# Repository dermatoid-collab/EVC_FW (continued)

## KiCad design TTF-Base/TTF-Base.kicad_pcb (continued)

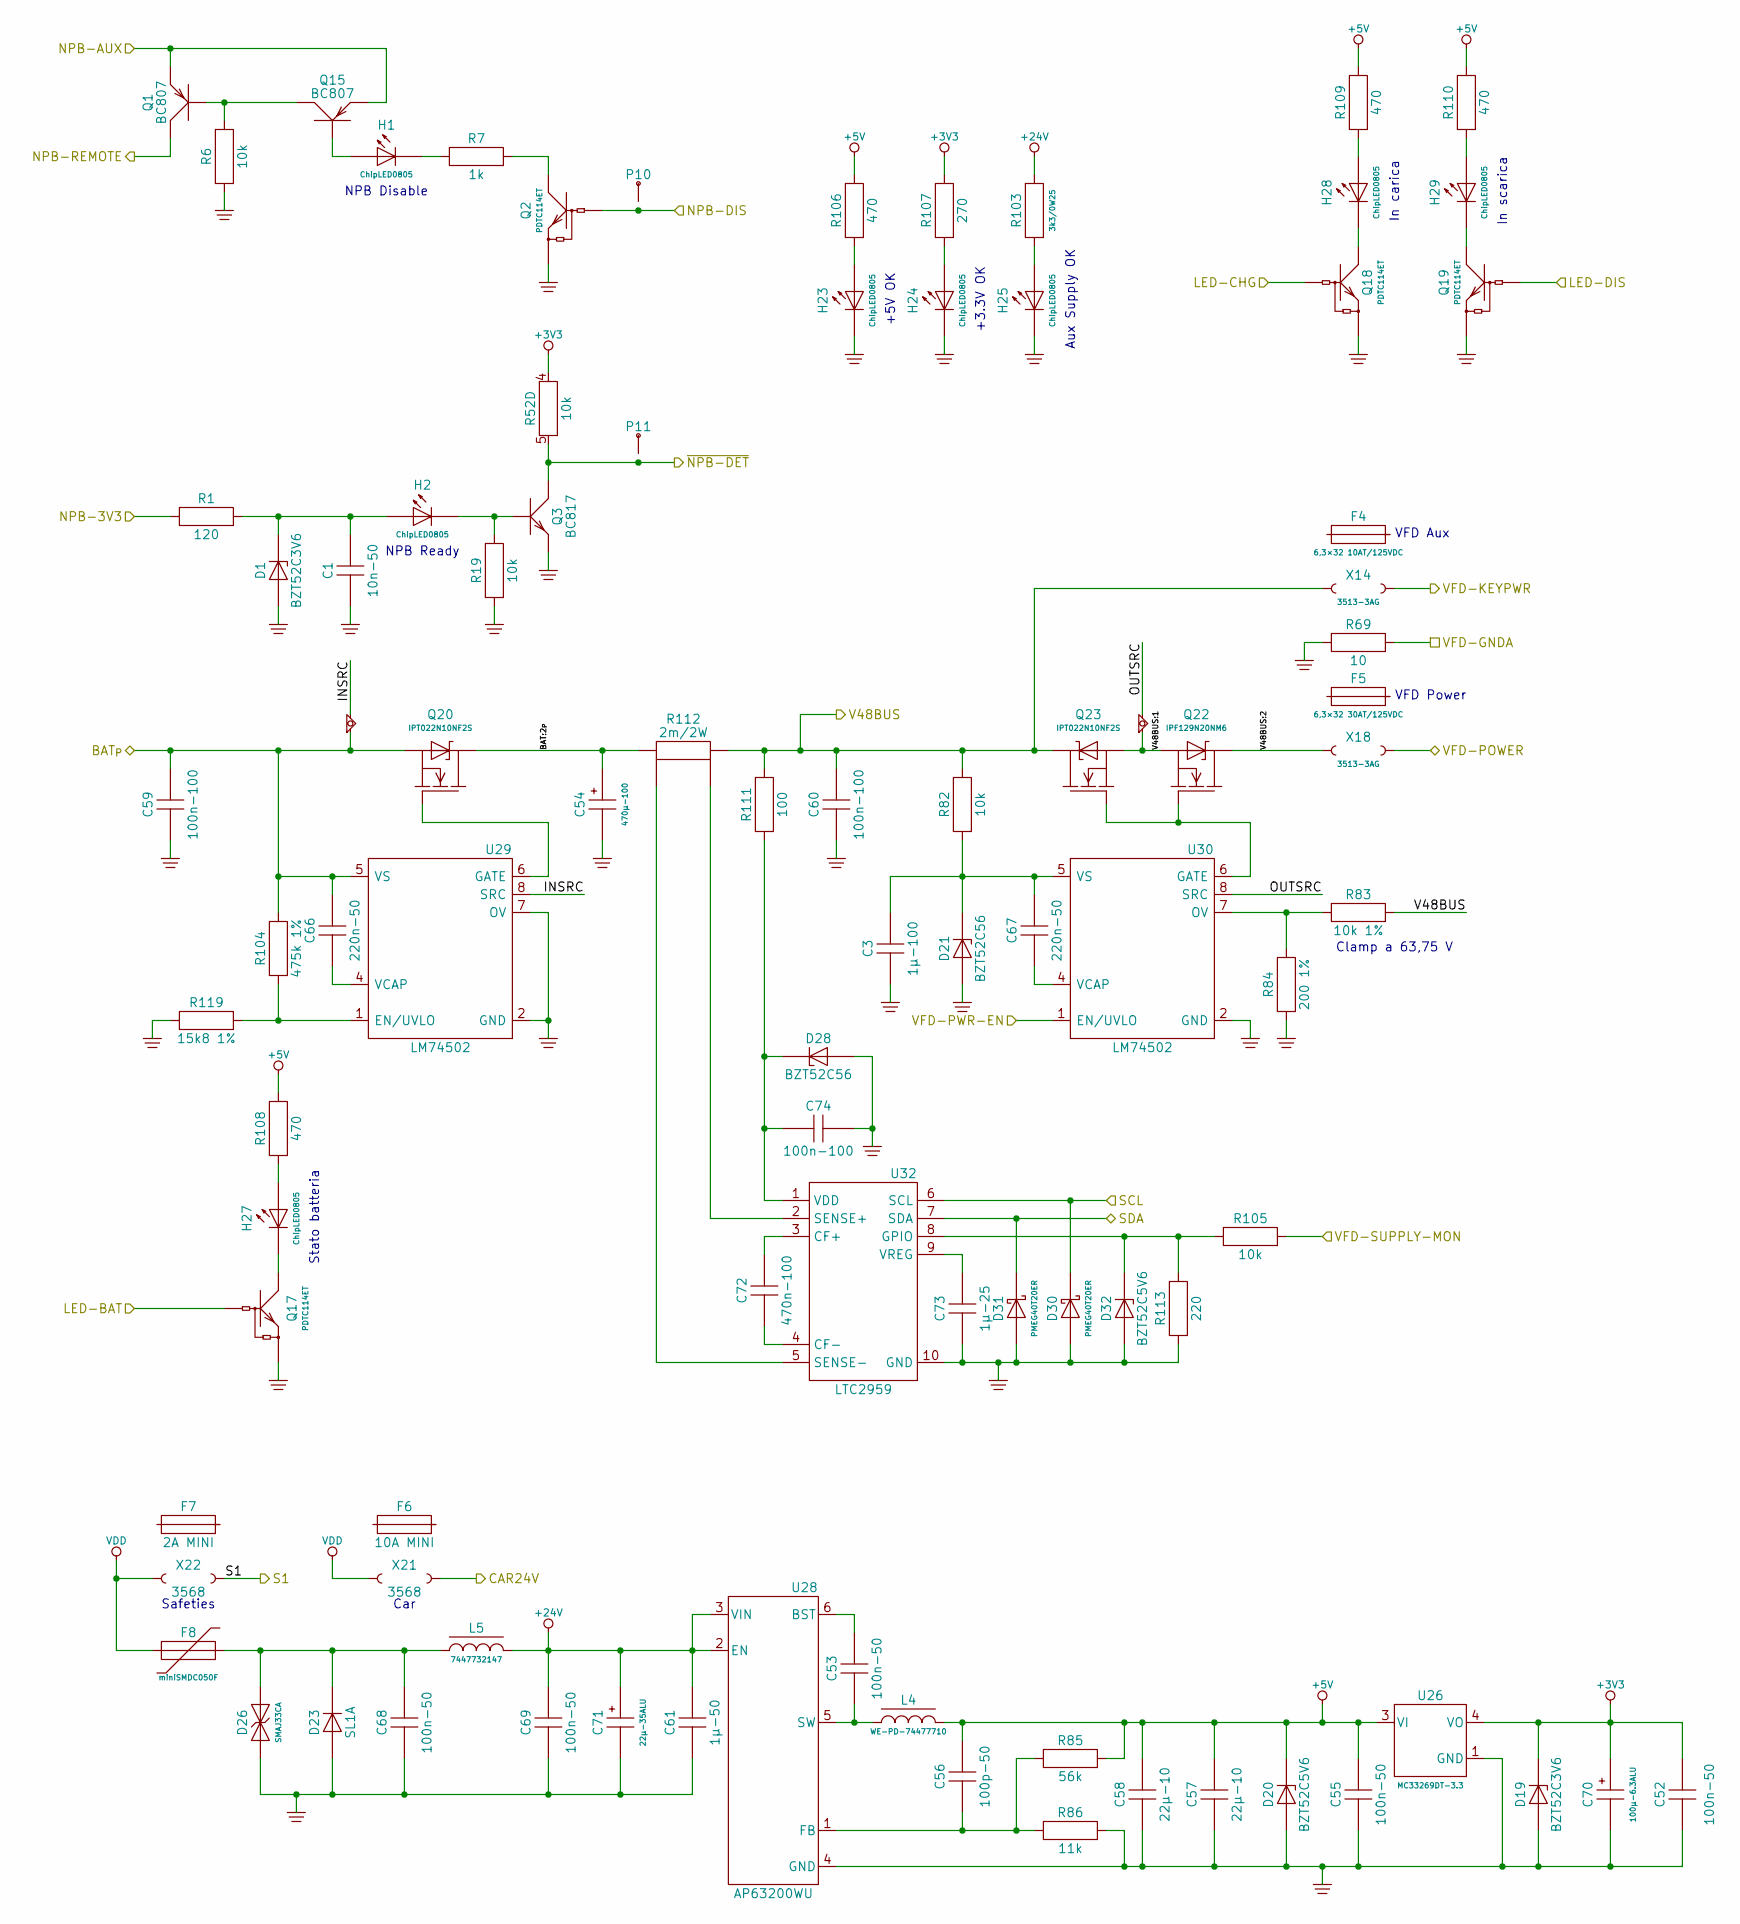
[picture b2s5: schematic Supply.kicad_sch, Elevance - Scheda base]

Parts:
C1: 10n-50; C0603
C3: 1µ-100; C1206
C52, C53, C55, C68, C69: 100n-50; C0603
C54: 470µ-100; CPAlu-12.5x25P5
C56: 100p-50; C0603
C57, C58: 22µ-10; C0805
C59, C60, C74: 100n-100; C1206
C61: 1µ-50; C1206
C66, C67: 220n-50; C0603
C70: 100µ-6.3ALU; CPV-5x5.5
C71: 22µ-35ALU; CPV-5x5.5
C72: 470n-100; C0805
C73: 1µ-25; C0603
D1, D19: BZT52C3V6; SOD123
D20, D32: BZT52C5V6; SOD123
D21, D28: BZT52C56; SOD123
D23: SL1A; SOD123FL
D26: SMAJ33CA; DO214AC-NPOL
D30, D31: PMEG40T20ER; NXP-SOD123W
EQUI1, EQUI4: EQUIPOT; Equipot-04
F4: 6,3×32 10AT/125VDC; 3AG-Fuse
F5: 6,3×32 30AT/125VDC; 3AG-Fuse
F6: 10A MINI; MINI-Fuse
F7: 2A MINI; MINI-Fuse
F8: miniSMDC050F; miniSMDC
H1, H2, H23, H24, H25, H27, H28, H29: ChipLED0805; Chipled-0805
L4: WE-PD-74477710; WE-PD-7345A
L5: 7447732147; WE-PD2-3521
P10, P11: TestPoint; PinTst
Q1, Q15: BC807; TO236-BEC
Q2, Q17, Q18, Q19: PDTC114ET; TO236-BEC
Q3: BC817; TO236-BEC
Q20, Q23: IPT022N10NF2S; Infineon-PG-HSOF-8-10
Q22: IPF129N20NM6; Infineon-TO263-7-GSSxSSSD
R1: 120; R0603
R6, R19, R82, R105: 10k; R0603
R7: 1k; R0603
R52: 10k; KMY-RAC164D
R69: 10; R0603
R83: 10k 1%; R0603
R84: 200 1%; R0603
R85: 56k; R0603
R86: 11k; R0603
R103: 3k3/0W25; R1206
R104: 475k 1%; R0603
R106, R108, R109, R110: 470; R0603
R107: 270; R0603
R111: 100; R0603
R112: 2m/2W; R2512K
R113: 220; R0603
R119: 15k8 1%; R0603
U26: MC33269DT-3.3; TO252AA
U28: AP63200WU; MO193AA
U29, U30: LM74502; MO193BA
U32: LTC2959; MO229W3020D2-NOPAD
X14, X18: 3513-3AG; Keystone-3513-3AG
X21, X22: 3568; Keystone-3568

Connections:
+3V3: C52.2, C70.+, D19.K, R52.4, R107.1, U26.4 (VO); also elsewhere on the board
+5V: C55.2, C56.2, C57.2, C58.2, D20.K, L4.2, R85.1, R106.1, R108.1, R109.1, R110.1, U26.3 (VI); also elsewhere on the board
+24V: C61.2, C69.2, C71.+, L5.2, R103.2, U28.2 (EN), U28.3 (VIN); also elsewhere on the board
/CAR24V: X21.2; also elsewhere on the board
/Logica/LED-BAT: Q17.B; also elsewhere on the board
/Logica/LED-CHG: Q18.B; also elsewhere on the board
/Logica/LED-DIS: Q19.B; also elsewhere on the board
/Logica/NPB-DIS: P10.1 (P1_1), Q2.B; also elsewhere on the board
/Logica/SCL: D30.K, U32.6 (SCL); also elsewhere on the board
/Logica/SDA: D31.K, U32.7 (SDA); also elsewhere on the board
/Logica/VFD-PWR-EN: U30.1 (EN/UVLO); also elsewhere on the board
/Logica/~NPB-DET: P11.1 (P1_1), Q3.C, R52.5; also elsewhere on the board
/S1: X22.2; also elsewhere on the board
/Supply/BAT:2_{P}: C54.+, Q20.D, R112.2
/Supply/BAT_{P}: C59.2, C66.2, EQUI1.1, Q20.S, R104.1, U29.5 (VS); also elsewhere on the board
/Supply/INSRC: EQUI1.2, U29.8 (SRC)
/Supply/NPB-3V3: R1.2; also elsewhere on the board
/Supply/NPB-AUX: Q1.E, Q15.E; also elsewhere on the board
/Supply/NPB-REMOTE: Q1.C; also elsewhere on the board
/Supply/OUTSRC: EQUI4.2, U30.8 (SRC)
/Supply/V48BUS: C60.2, Q23.D, R82.1, R83.1, R111.1, R112.1, X14.1; also elsewhere on the board
/Supply/V48BUS:1: EQUI4.1, Q22.S, Q23.S
/Supply/V48BUS:2: Q22.D, X18.1
/VFD-GNDA: R69.1; also elsewhere on the board
/VFD-KEYPWR: X14.2; also elsewhere on the board
/VFD-POWER: X18.2; also elsewhere on the board
/VFD-SUPPLY-MON: R105.1; also elsewhere on the board
GND: C1.1, C3.1, C52.1, C54.-, C55.1, C57.1, C58.1, C59.1, C60.1, C61.1, C68.1, C69.1, C70.-, C71.-, C73.1, C74.2, D1.A, D19.A, D20.A, D21.A, D23.A, D26.1, D28.A, D30.A, D31.A, D32.A, H23.K, H24.K, H25.K, Q2.E, Q3.E, Q17.E, Q18.E, Q19.E, R6.2, R19.2, R69.2, R84.2, R86.1, R113.2, R119.1, U26.1 (GND), U28.4 (GND), U29.2 (GND), U29.7 (OV), U30.2 (GND), U32.10 (GND); also elsewhere on the board
unnamed: C1.2, D1.K, H2.A, R1.1
unnamed: C68.2, D23.K, D26.2, F8.2, L5.1
unnamed: H1.A, Q15.B
unnamed: H1.K, R7.2
unnamed: H2.K, Q3.B, R19.1
unnamed: H23.A, R106.2
unnamed: H24.A, R107.2
unnamed: H25.A, R103.1
unnamed: H27.A, R108.2
unnamed: H27.K, Q17.C
unnamed: H28.A, R109.2
unnamed: H28.K, Q18.C
unnamed: H29.A, R110.2
unnamed: H29.K, Q19.C
unnamed: Q1.B, Q15.C, R6.1
unnamed: Q2.C, R7.1
unnamed: C53.2, U28.6 (BST)
unnamed: C56.1, R85.2, R86.2, U28.1 (FB)
unnamed: C53.1, L4.1, U28.5 (SW)
unnamed: R104.2, R119.2, U29.1 (EN/UVLO)
unnamed: Q20.G, U29.6 (GATE)
unnamed: C66.1, U29.4 (VCAP)
unnamed: Q22.G, Q23.G, U30.6 (GATE)
unnamed: R83.2, R84.1, U30.7 (OV)
unnamed: C67.1, U30.4 (VCAP)
unnamed: C3.2, C67.2, D21.K, R82.2, U30.5 (VS)
unnamed: C72.2, U32.3 (CF+)
unnamed: C72.1, U32.4 (CF-)
unnamed: D32.K, R105.2, R113.1, U32.8 (GPIO)
unnamed: R112.3, U32.2 (SENSE+)
unnamed: R112.4, U32.5 (SENSE-)
unnamed: C74.1, D28.K, R111.2, U32.1 (VDD)
unnamed: C73.2, U32.9 (VREG)
VDD: F8.1, X21.1, X22.1; also elsewhere on the board

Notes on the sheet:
NPB Disable
Safeties
Clamp a 63,75 V
+3.3V OK
VFD Power
NPB Ready
+5V OK
Aux Supply OK
Stato batteria
Car
In scarica
VFD Aux
In carica

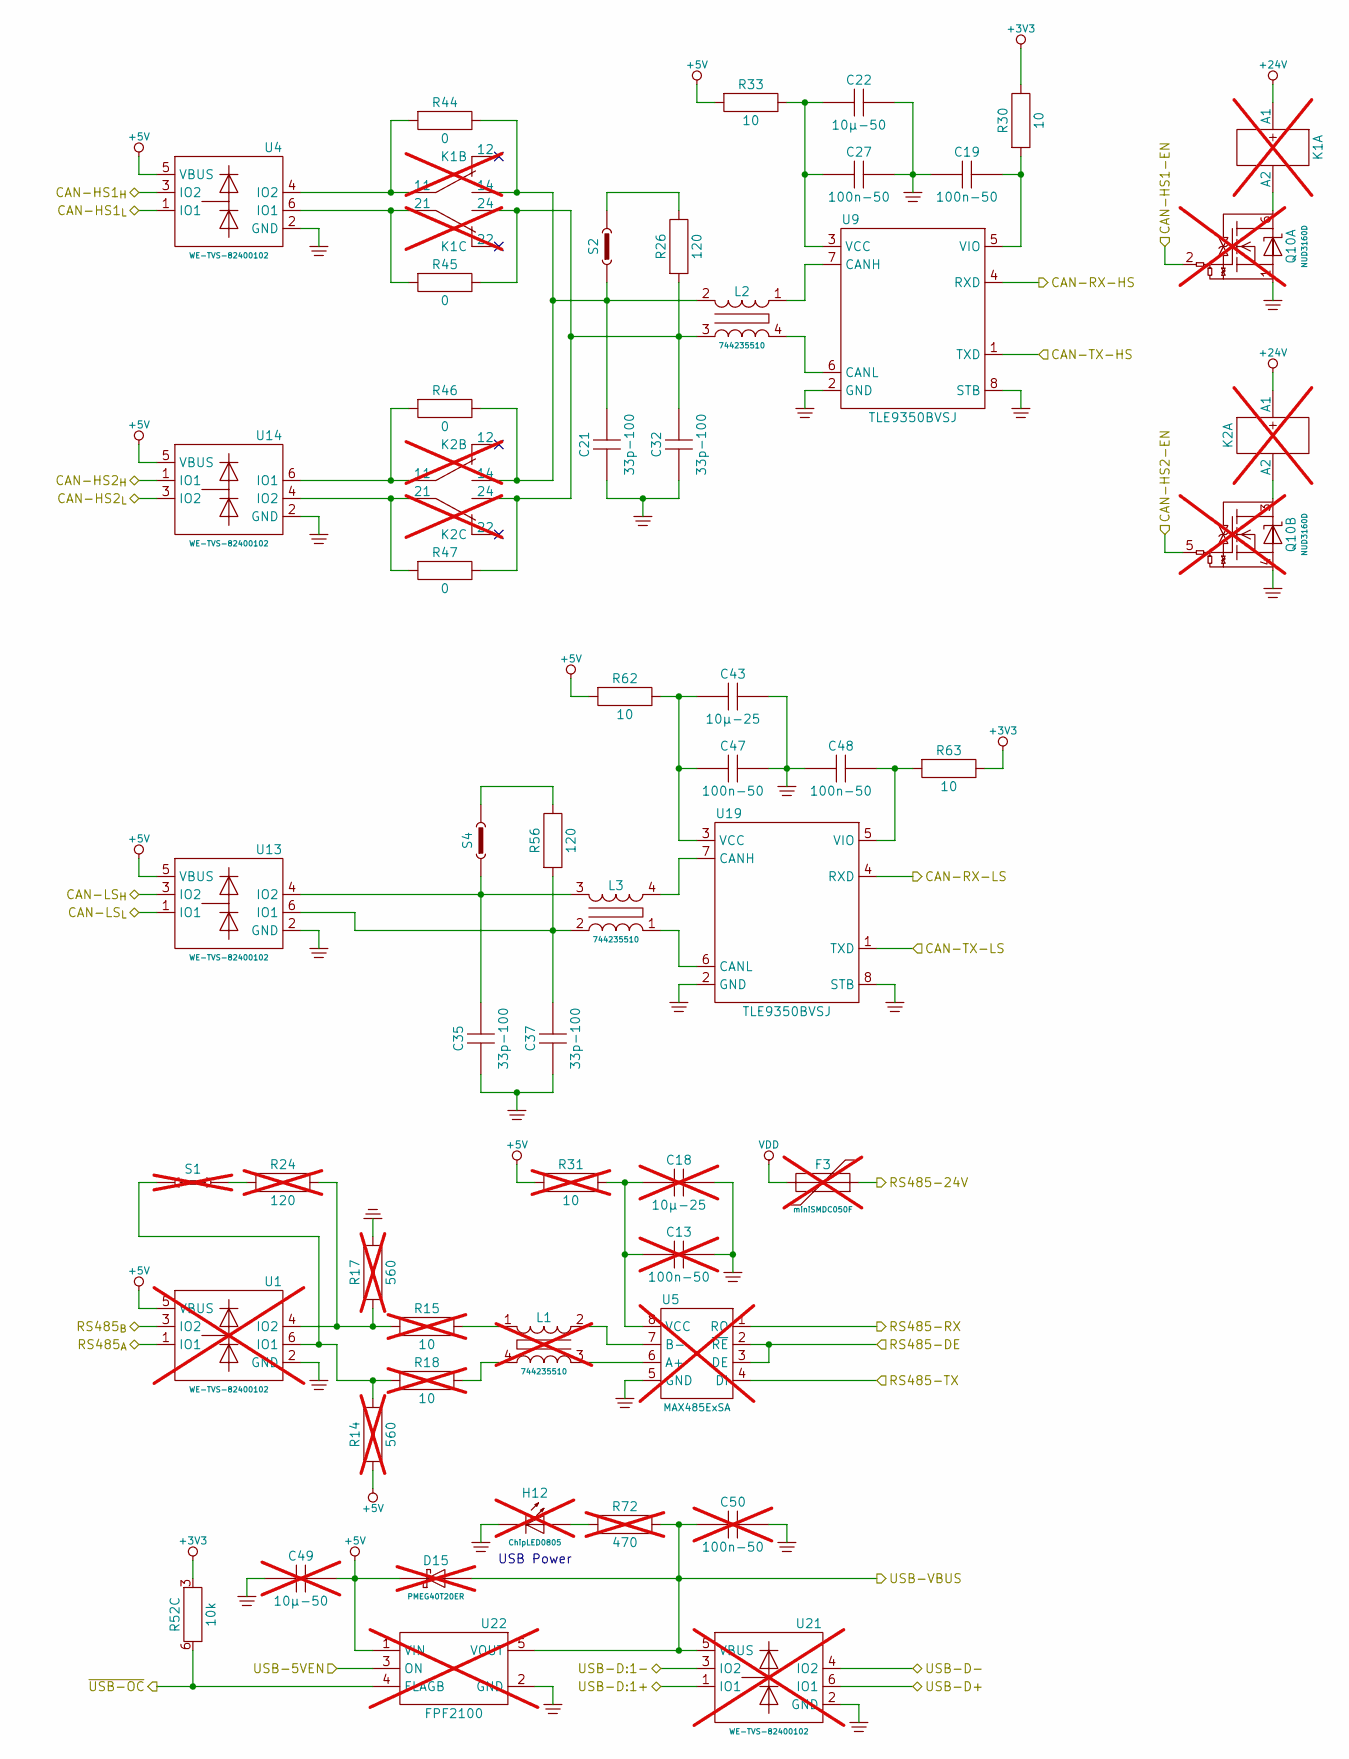
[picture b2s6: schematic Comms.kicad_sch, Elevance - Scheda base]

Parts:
C13, C50: 100n-50; C0603; not fitted
C18: 10µ-25; C0805; not fitted
C19, C27, C47, C48: 100n-50; C0603
C21, C32, C35, C37: 33p-100; C0603
C22: 10µ-50; C1206
C43: 10µ-25; C0805
C49: 10µ-50; C1206; not fitted
D15: PMEG40T20ER; NXP-SOD123W; not fitted
F3: miniSMDC050F; miniSMDC; not fitted
H12: ChipLED0805; Chipled-0805; not fitted
K1, K2: AGN20024; Panasonic-AGN200; not fitted
L1: 744235510; WE-CNSW-1812; not fitted
L2, L3: 744235510; WE-CNSW-1812
Q10: NUD3160D; MO193AA; not fitted
R14, R17: 560; R0603; not fitted
R15, R18, R31: 10; R0603; not fitted
R24: 120; R1210; not fitted
R26, R56: 120; R1210
R30, R33, R62, R63: 10; R0603
R44, R45, R46, R47: 0; R0603
R52: 10k; KMY-RAC164D
R72: 470; R0603; not fitted
S1: Jumper-2.54; not fitted
S2, S4: Jumper-2.54
U1, U21: WE-TVS-82400102; MO178AB; not fitted
U4, U13, U14: WE-TVS-82400102; MO178AB
U5: MAX485ExSA; MS012AA; not fitted
U9, U19: TLE9350BVSJ; MS012AA
U22: FPF2100; MO178AA; not fitted

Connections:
+3V3: R30.1, R52.3, R63.1; also elsewhere on the board
+5V: C49.2, D15.K, R14.2, R31.2, R33.2, R62.2, U1.5 (VBUS), U4.5 (VBUS), U13.5 (VBUS), U14.5 (VBUS), U22.1 (VIN); also elsewhere on the board
+24V: K1.A1, K2.A1; also elsewhere on the board
/CAN-HS1_{H}: U4.3 (IO2); also elsewhere on the board
/CAN-HS1_{L}: U4.1 (IO1); also elsewhere on the board
/CAN-HS2_{H}: U14.1 (IO1); also elsewhere on the board
/CAN-HS2_{L}: U14.3 (IO2); also elsewhere on the board
/CAN-HS-RX: U9.4 (RXD); also elsewhere on the board
/CAN-HS-TX: U9.1 (TXD); also elsewhere on the board
/CAN-LS_{H}: U13.3 (IO2); also elsewhere on the board
/CAN-LS_{L}: U13.1 (IO1); also elsewhere on the board
/Comms/CAN-HS1-EN: Q10.2 (G); also elsewhere on the board
/Comms/CAN-HS2-EN: Q10.5 (G); also elsewhere on the board
/Comms/CAN-RX-LS: U19.4 (RXD); also elsewhere on the board
/Comms/CAN-TX-LS: U19.1 (TXD); also elsewhere on the board
/Comms/RS485-24V: F3.2; also elsewhere on the board
/Comms/RS485-DE: U5.2 (~RE), U5.3 (DE); also elsewhere on the board
/Comms/RS485-RX: U5.1 (RO); also elsewhere on the board
/Comms/RS485-TX: U5.4 (DI); also elsewhere on the board
/Comms/RS485_{A}: U1.1 (IO1); also elsewhere on the board
/Comms/RS485_{B}: U1.3 (IO2); also elsewhere on the board
/Comms/USB-5VEN: U22.3 (ON); also elsewhere on the board
/Comms/USB-D+: U21.6 (IO1); also elsewhere on the board
/Comms/USB-D-: U21.4 (IO2); also elsewhere on the board
/Comms/USB-D:1+: U21.1 (IO1); also elsewhere on the board
/Comms/USB-D:1-: U21.3 (IO2); also elsewhere on the board
/Comms/~USB-OC: R52.6, U22.4 (FLAGB); also elsewhere on the board
/USB-VBUS: C50.1, D15.A, R72.1, U21.5 (VBUS), U22.5 (VOUT); also elsewhere on the board
GND: C13.2, C18.2, C19.2, C21.1, C22.1, C27.1, C32.1, C35.1, C37.1, C43.2, C47.1, C48.2, C49.1, C50.2, H12.K, Q10.1 (4), Q10.4, R17.1, U1.2 (GND), U4.2 (GND), U5.5 (GND), U9.2 (GND), U9.8 (STB), U13.2 (GND), U14.2 (GND), U19.2 (GND), U19.8 (STB), U21.2 (GND), U22.2 (GND); also elsewhere on the board
unnamed: C21.2, K1.14, K2.14, L2.2, R44.1, R46.1, S2.1
unnamed: C32.2, K1.24, K2.24, L2.3, R26.2, R45.1, R47.1
unnamed: H12.A, R72.2
unnamed: K2.11, R46.2, U14.6 (IO1)
unnamed: K2.21, R47.2, U14.4 (IO2)
unnamed: L1.1, R15.1
unnamed: L1.4, R18.1
unnamed: K1.A2, Q10.6 (D)
unnamed: K2.A2, Q10.3 (D)
unnamed: R24.2, S1.1
unnamed: R26.1, S2.2
unnamed: R56.1, S4.2
unnamed: L1.3, U5.6 (A+)
unnamed: L1.2, U5.7 (B-)
unnamed: C13.1, C18.1, R31.1, U5.8 (VCC)
unnamed: L2.1, U9.7 (CANH)
unnamed: L2.4, U9.6 (CANL)
unnamed: C22.2, C27.2, R33.1, U9.3 (VCC)
unnamed: C19.1, R30.2, U9.5 (VIO)
unnamed: L3.4, U19.7 (CANH)
unnamed: L3.1, U19.6 (CANL)
unnamed: C43.1, C47.2, R62.1, U19.3 (VCC)
unnamed: C48.1, R63.2, U19.5 (VIO)
VDD: F3.1; also elsewhere on the board

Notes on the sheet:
USB Power

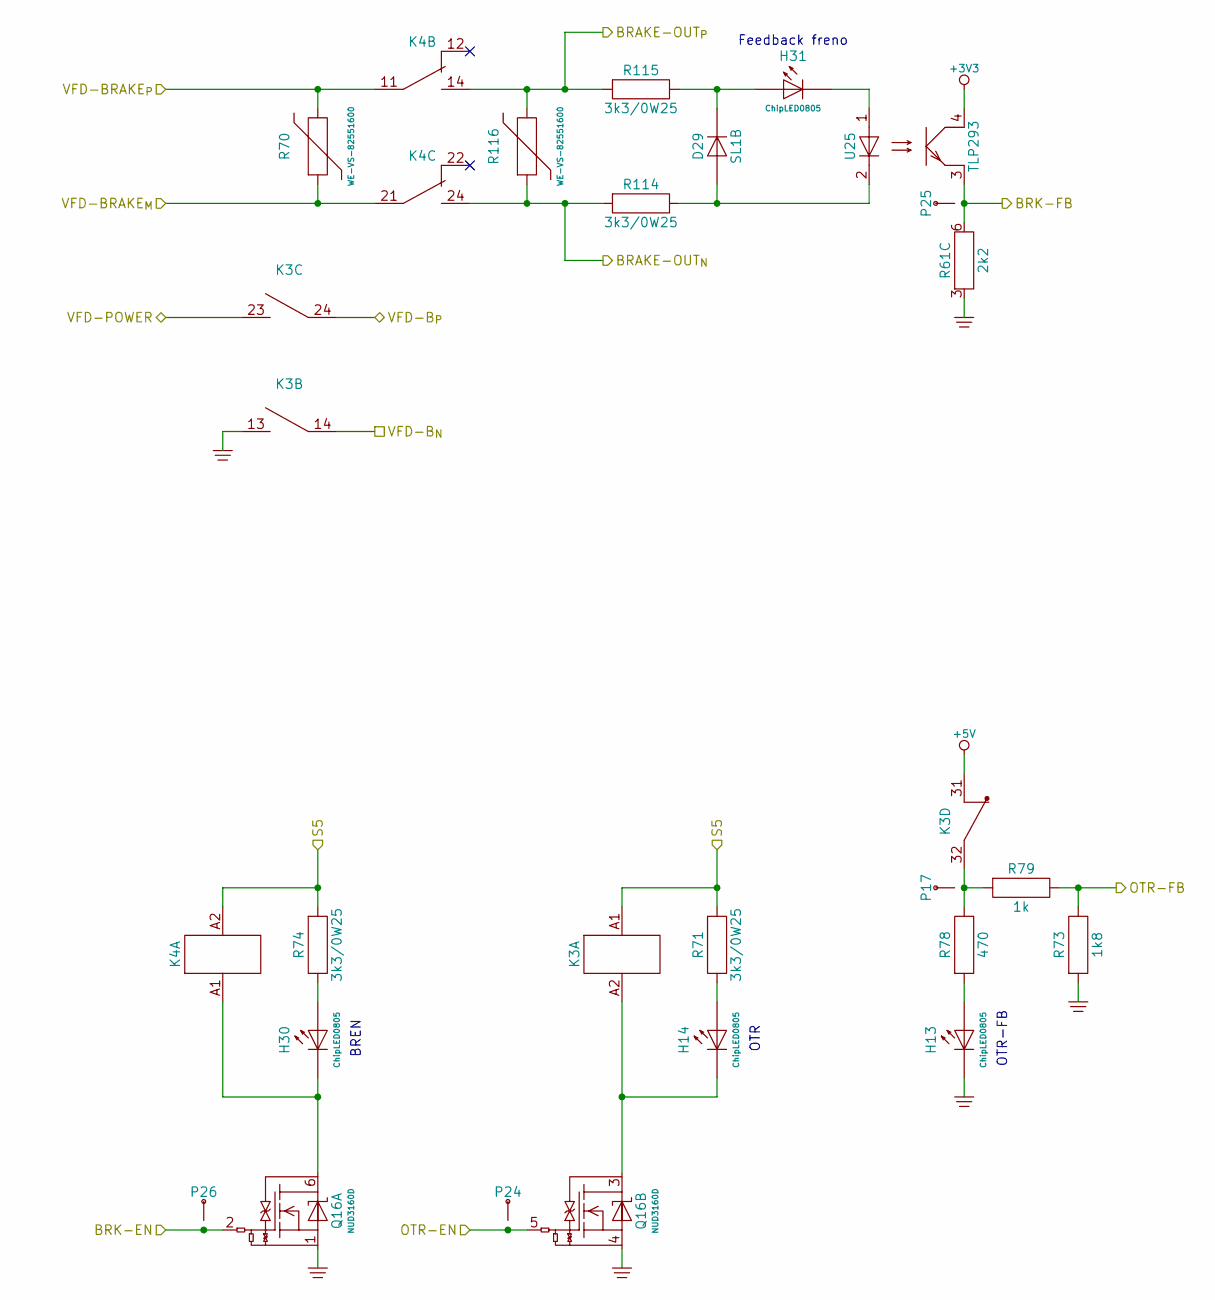
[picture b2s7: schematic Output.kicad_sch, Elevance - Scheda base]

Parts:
D29: SL1B; SOD123FL
H13, H14, H30, H31: ChipLED0805; Chipled-0805
K3: AHES4192; Panasonic-AHES4x9xx
K4: G2RL-2; Omron-G2RL-2
P17, P24, P25, P26: TestPoint; PinTst
Q16: NUD3160D; MO193AA
R61: 2k2; KMY-RAC164D
R70, R116: WE-VS-82551600; WE-VS-1206
R71, R74, R114, R115: 3k3/0W25; R1206
R73: 1k8; R0603
R78: 470; R0603
R79: 1k; R0603
U25: TLP293; Toshiba-11-3C1

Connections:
+3V3: U25.4 (C); also elsewhere on the board
+5V: K3.31; also elsewhere on the board
/Logica/BRK-EN: P26.1 (P1_1), Q16.2 (G); also elsewhere on the board
/Logica/BRK-FB: P25.1 (P1_1), R61.6, U25.3 (E); also elsewhere on the board
/Logica/OTR-EN: P24.1 (P1_1), Q16.5 (G); also elsewhere on the board
/Logica/OTR-FB: R73.1, R79.1; also elsewhere on the board
/Output/BRAKE-OUT_{N}: K4.24, R114.2, R116.1; also elsewhere on the board
/Output/BRAKE-OUT_{P}: K4.14, R115.2, R116.2; also elsewhere on the board
/Output/VFD-BRAKE_{M}: K4.21, R70.1; also elsewhere on the board
/Output/VFD-BRAKE_{P}: K4.11, R70.2; also elsewhere on the board
/Output/VFD-B_{N}: K3.14; also elsewhere on the board
/S5: K3.A1, K4.A2, R71.2, R74.2; also elsewhere on the board
/VFD-POWER: K3.23; also elsewhere on the board
/VFD-SUPPLY-MON: K3.24; also elsewhere on the board
GND: H13.K, K3.13, Q16.1 (4), Q16.4, R61.3, R73.2; also elsewhere on the board
unnamed: D29.K, H31.A, R115.1
unnamed: H13.A, R78.2
unnamed: H14.A, R71.1
unnamed: H30.A, R74.1
unnamed: K3.32, P17.1 (P1_1), R78.1, R79.2
unnamed: H30.K, K4.A1, Q16.6 (D)
unnamed: H14.K, K3.A2, Q16.3 (D)
unnamed: H31.K, U25.1 (A)
unnamed: D29.A, R114.1, U25.2 (K)

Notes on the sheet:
OTR-FB
Feedback freno
OTR
BREN

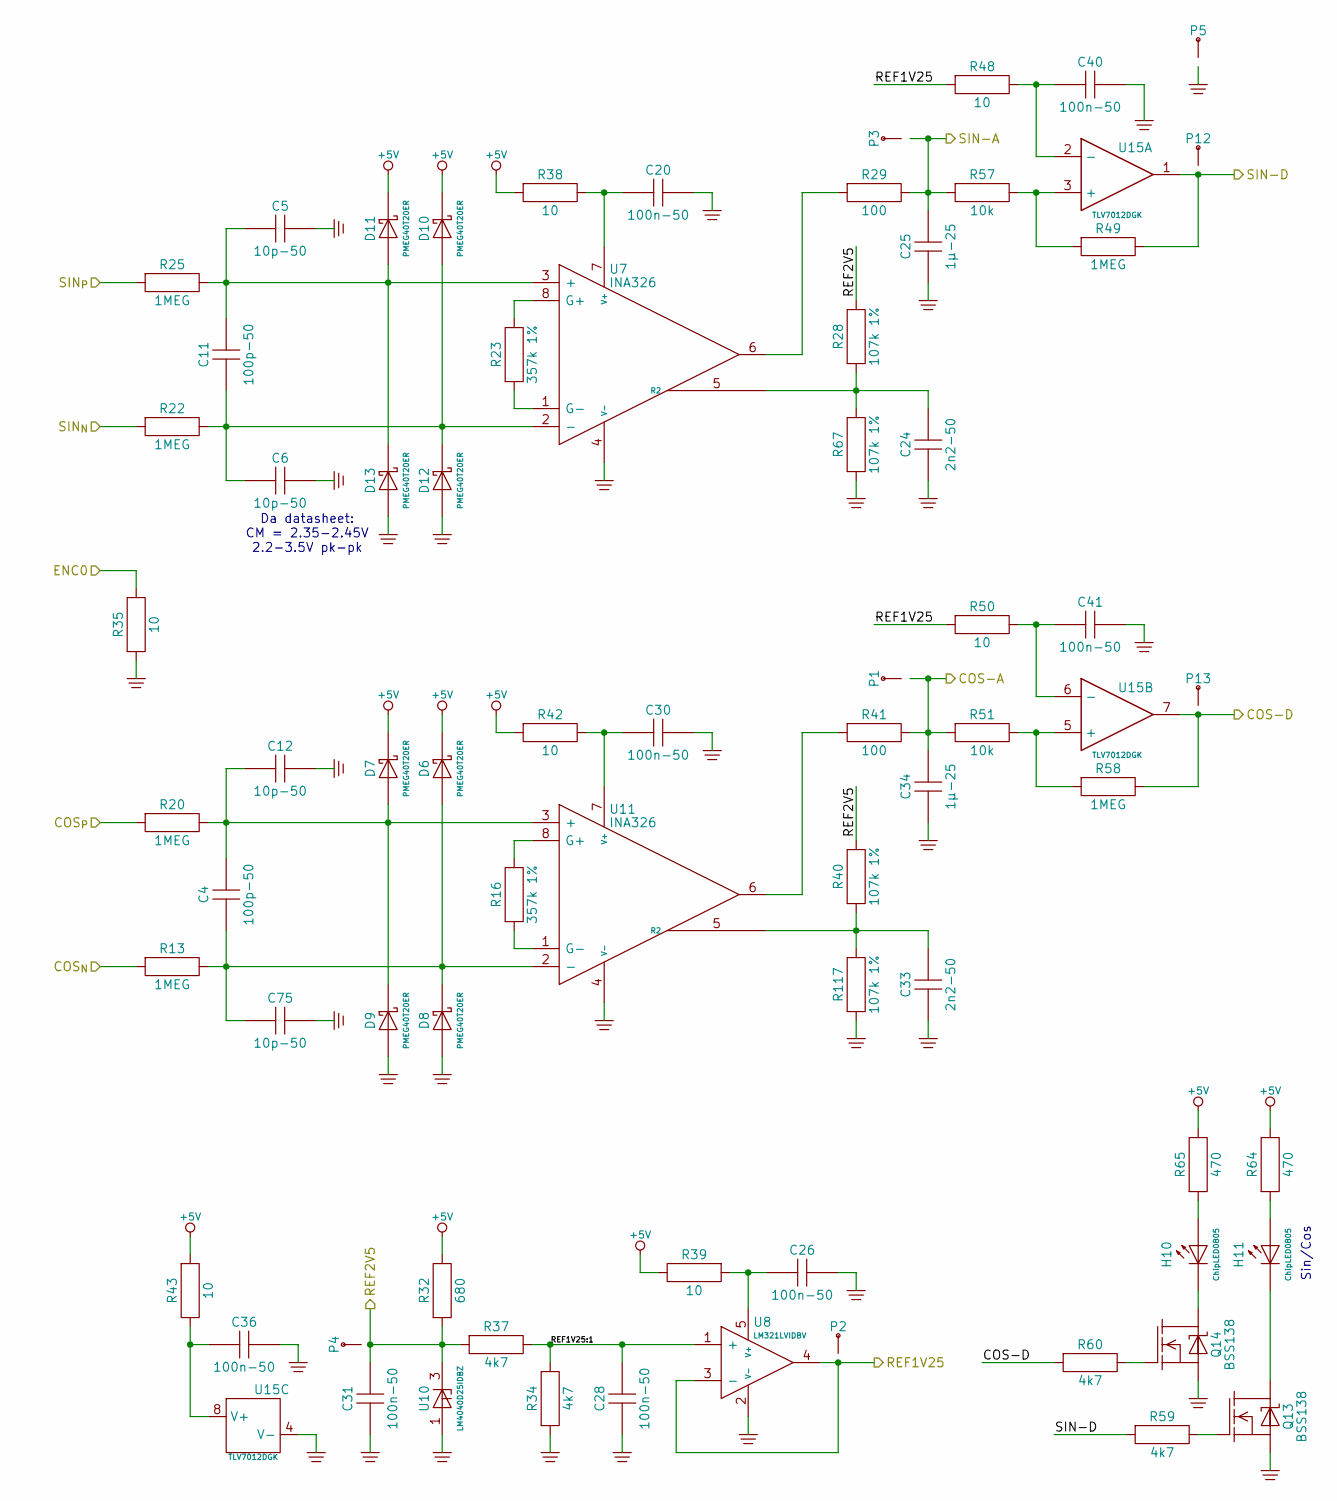
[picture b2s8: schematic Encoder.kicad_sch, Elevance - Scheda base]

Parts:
C4, C11: 100p-50; C0603
C5, C6, C12, C75: 10p-50; C0603
C20, C26, C28, C30, C31, C36, C40, C41: 100n-50; C0603
C24, C33: 2n2-50; C0603
C25, C34: 1µ-25; C0603
D6, D7, D8, D9, D10, D11, D12, D13: PMEG40T20ER; NXP-SOD123W
H10, H11: ChipLED0805; Chipled-0805
P1, P2, P3, P4, P5, P12, P13: TestPoint; PinTst
Q13, Q14: BSS138; TO236-GSD
R13, R20, R22, R25, R49, R58: 1MEG; R0603
R16, R23: 357k 1%; R0603
R28, R40, R67, R117: 107k 1%; R0603
R29, R41: 100; R0603
R32: 680; R0603
R34, R37, R59, R60: 4k7; R0603
R35, R38, R39, R42, R43, R48, R50: 10; R0603
R51, R57: 10k; R0603
R64, R65: 470; R0603
U7, U11: INA326; MO187AA
U8: LM321LVIDBV; MO178AA
U10: LM4040D25IDBZ; TO236
U15: TLV7012DGK; MO187AA

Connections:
+5V: D6.K, D7.K, D10.K, D11.K, R32.1, R38.2, R39.1, R42.2, R43.2, R64.1, R65.1; also elsewhere on the board
/COS_{N}: R13.2; also elsewhere on the board
/COS_{P}: R20.2; also elsewhere on the board
/ENC0: R35.1; also elsewhere on the board
/Encoder/COS-A: C34.2, P1.1 (P1_1), R41.1, R51.2; also elsewhere on the board
/Encoder/COS-D: P13.1 (P1_1), R58.1, R60.2, U15.7; also elsewhere on the board
/Encoder/REF1V25: P2.1 (P1_1), R48.2, R50.2, U8.3 (-), U8.4; also elsewhere on the board
/Encoder/REF1V25:1: C28.2, R34.1, R37.1, U8.1 (+)
/Encoder/REF2V5: C31.2, P4.1 (P1_1), R28.1, R32.2, R37.2, R40.1, U10.3 (K); also elsewhere on the board
/Encoder/SIN-A: C25.2, P3.1 (P1_1), R29.1, R57.2; also elsewhere on the board
/Encoder/SIN-D: P12.1 (P1_1), R49.1, R59.2, U15.1; also elsewhere on the board
/SIN_{N}: R22.2; also elsewhere on the board
/SIN_{P}: R25.2; also elsewhere on the board
GND: C5.2, C6.2, C12.2, C20.2, C24.1, C25.1, C26.2, C28.1, C30.2, C31.1, C33.1, C34.1, C36.2, C40.2, C41.2, C75.2, D8.A, D9.A, D12.A, D13.A, P5.1 (P1_1), Q13.S, Q14.S, R34.2, R35.2, R67.2, R117.2, U7.4 (V-), U8.2 (V-), U10.1 (A), U11.4 (V-), U15.4 (V-); also elsewhere on the board
unnamed: H10.A, R65.2
unnamed: H10.K, Q14.D
unnamed: H11.A, R64.2
unnamed: H11.K, Q13.D
unnamed: Q13.G, R59.1
unnamed: Q14.G, R60.1
unnamed: R29.2, U7.6
unnamed: R41.2, U11.6
unnamed: C5.1, C11.2, D11.A, D13.K, R25.1, U7.3 (+)
unnamed: C6.1, C11.1, D10.A, D12.K, R22.1, U7.2 (-)
unnamed: R23.1, U7.8 (G+)
unnamed: R23.2, U7.1 (G-)
unnamed: C24.2, R28.2, R67.1, U7.5 (R2)
unnamed: C20.1, R38.1, U7.7 (V+)
unnamed: C26.1, R39.2, U8.5 (V+)
unnamed: C4.2, C12.1, D7.A, D9.K, R20.1, U11.3 (+)
unnamed: C4.1, C75.1, D6.A, D8.K, R13.1, U11.2 (-)
unnamed: R16.1, U11.8 (G+)
unnamed: R16.2, U11.1 (G-)
unnamed: C33.2, R40.2, R117.1, U11.5 (R2)
unnamed: C30.1, R42.1, U11.7 (V+)
unnamed: C36.1, R43.1, U15.8 (V+)

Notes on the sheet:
Da datasheet: CM = 2.35-2.45V 2.2-3.5V pk-pk
Sin/Cos

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
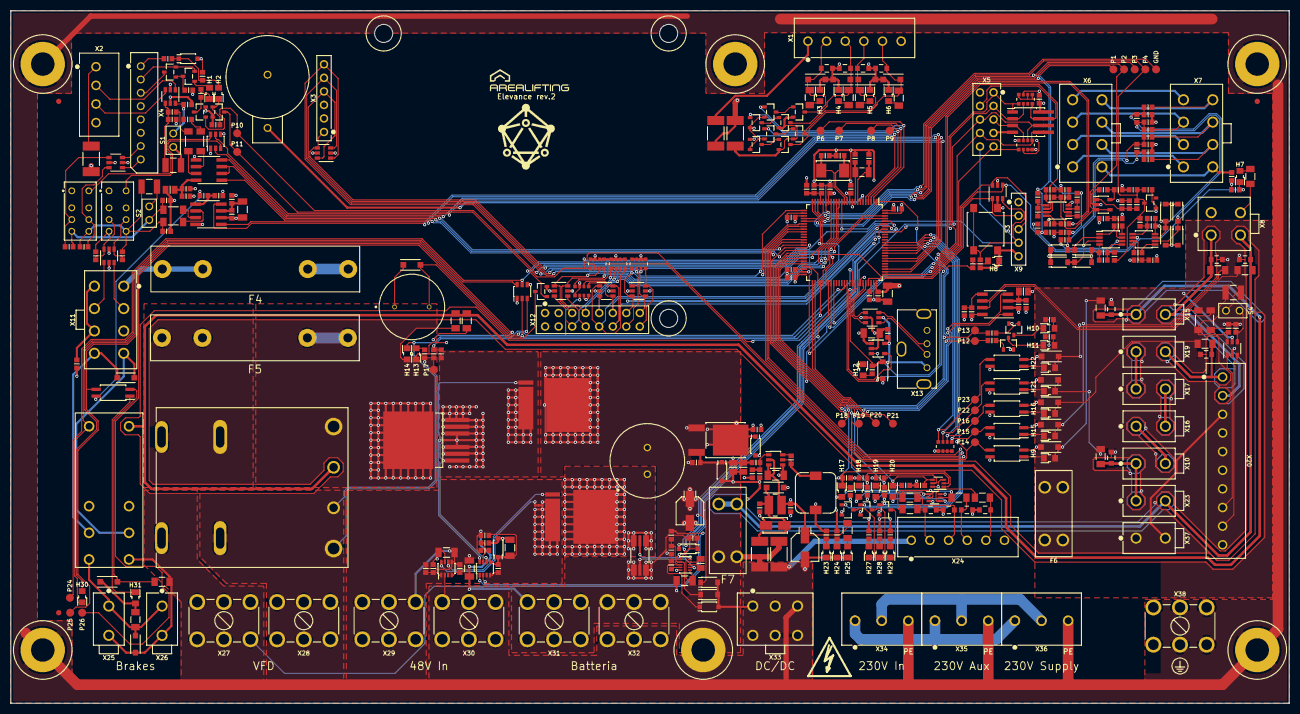
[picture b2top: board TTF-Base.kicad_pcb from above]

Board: 4 copper layers, 240.0 x 130.0 mm, 420 parts (0 on the bottom side), 269 nets.

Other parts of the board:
Flash: Flash-Small
Logo-UDEC: Logo-UDEC; Logo-UDEC-Silk
PE: PE; PE-3mm
UDEC.HMI: UDEC.HMI
ZZZ1: Logo-AreaLifting

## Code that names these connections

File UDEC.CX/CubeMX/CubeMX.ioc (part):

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Mcu.Name=STM32F446V(C-E)Tx
Mcu.Package=LQFP100
Mcu.UserName=STM32F446VCTx
PA0-WKUP.GPIOParameters=GPIO_Label
PA0-WKUP.GPIO_Label=ONEWIRE_IN0
PA0-WKUP.Signal=S_TIM2_CH1_ETR
PA1.GPIOParameters=GPIO_Label
PA1.GPIO_Label=SPIF_SIO3
PA1.Mode=Single Bank 1
PA1.Signal=QUADSPI_BK1_IO3
PA10.Mode=Asynchronous
PA10.Signal=USART1_RX
PA11.GPIOParameters=GPIO_Label
PA11.GPIO_Label=CAN_RX
PA11.Mode=CAN_Activate
PA11.Signal=CAN1_RX
PA12.GPIOParameters=GPIO_Label
PA12.GPIO_Label=CAN_TX
PA12.Mode=CAN_Activate
PA12.Signal=CAN1_TX
PA13.GPIOParameters=GPIO_Label
PA13.GPIO_Label=SWDIO
PA13.Mode=Serial_Wire
PA13.Signal=SYS_JTMS-SWDIO
PA14.GPIOParameters=GPIO_Label
PA14.GPIO_Label=SWCLK
PA14.Mode=Serial_Wire
PA14.Signal=SYS_JTCK-SWCLK
PA15.GPIOParameters=GPIO_Label
PA15.GPIO_Label=ONEWIRE_LED
PA15.Signal=GPIO_Output
PA2.GPIOParameters=GPIO_Label
PA2.GPIO_Label=ONEWIRE_IN1
PA2.Signal=S_TIM2_CH3
PA3.GPIOParameters=GPIO_Label
PA3.GPIO_Label=NEOPIX_TX
PA3.Signal=S_TIM5_CH4
PA4.GPIOParameters=GPIO_Label
PA4.GPIO_Label=AUDIO_OUT
PA4.Signal=COMP_DAC1_group
PA5.GPIOParameters=GPIO_Label
PA5.GPIO_Label=VLIGHT_TRIM
PA5.Signal=COMP_DAC2_group
PA6.GPIOParameters=GPIO_Label
PA6.GPIO_Label=ISNS-U
PA6.Signal=ADCx_IN6
PA7.GPIOParameters=GPIO_Label
PA7.GPIO_Label=ISNS-V
PA7.Signal=ADCx_IN7
PA8.GPIOParameters=GPIO_Label
PA8.GPIO_Label=DEBUG
PA8.Signal=GPIO_Output
PA9.GPIOParameters=GPIO_Label
PA9.GPIO_Label=UART_TX
PA9.Mode=Asynchronous
PA9.Signal=USART1_TX
PB0.GPIOParameters=GPIO_Label
PB0.GPIO_Label=LPWM3_OUT
PB0.Signal=S_TIM3_CH3
PB1.GPIOParameters=GPIO_Label
PB1.GPIO_Label=LPWM4_OUT
PB1.Signal=S_TIM3_CH4
PB10.GPIOParameters=GPIO_Label
PB10.GPIO_Label=SPI_SCK
PB10.Mode=Full_Duplex_Master
PB10.Signal=SPI2_SCK
PB12.GPIOParameters=GPIO_Label
PB12.GPIO_Label=VFD_Y2
PB12.Signal=GPIO_Input
PB13.GPIOParameters=GPIO_Label
PB13.GPIO_Label=BRK_EN
PB13.Signal=GPIO_Output
PB14.GPIOParameters=GPIO_Label
PB14.GPIO_Label=BRK_EN_FB
PB14.Signal=GPIO_Input
PB15.GPIOParameters=GPIO_Label
PB15.GPIO_Label=BRK_FB2
PB15.Signal=GPIO_Input
PB2.GPIOParameters=GPIO_Label
PB2.GPIO_Label=SPIF_CLK
PB2.Mode=Single Bank 1
PB2.Signal=QUADSPI_CLK
PB3.GPIOParameters=GPIO_Speed,GPIO_Label
PB3.GPIO_Label=ONEWIRE_OUT
PB3.GPIO_Speed=GPIO_SPEED_FREQ_HIGH
PB3.Signal=S_TIM2_CH2
PB4.GPIOParameters=GPIO_Label
PB4.GPIO_Label=LPWM1_OUT
PB4.Signal=S_TIM3_CH1
PB5.GPIOParameters=GPIO_Label
PB5.GPIO_Label=LPWM2_OUT
PB5.Signal=S_TIM3_CH2
PB6.GPIOParameters=GPIO_Label
PB6.GPIO_Label=SPIF_NCS
PB6.Mode=Single Bank 1
PB6.Signal=QUADSPI_BK1_NCS
PB7.GPIOParameters=GPIO_Label
PB7.GPIO_Label=SDA
PB7.Mode=I2C
PB7.Signal=I2C1_SDA
PB8.GPIOParameters=GPIO_Label
PB8.GPIO_Label=SCL
PB8.Mode=I2C
PB8.Signal=I2C1_SCL
PB9.GPIOParameters=GPIO_Label
PB9.GPIO_Label=SPI_NSS
PB9.Signal=GPIO_Output
PC0.GPIOParameters=GPIO_Label
PC0.GPIO_Label=MOT_PTC
PC0.Signal=ADCx_IN10
PC1.GPIOParameters=GPIO_Label
PC1.GPIO_Label=SPI_MOSI
PC1.Mode=Full_Duplex_Master
PC1.Signal=SPI2_MOSI
PC10.GPIOParameters=GPIO_Label
PC10.GPIO_Label=SDIO_D2
PC10.Mode=SD_4_bits_Wide_bus
PC10.Signal=SDIO_D2
PC11.GPIOParameters=GPIO_Label
PC11.GPIO_Label=SDIO_D3
PC11.Mode=SD_4_bits_Wide_bus
PC11.Signal=SDIO_D3
PC12.GPIOParameters=GPIO_Label
PC12.GPIO_Label=SDIO_CK
PC12.Mode=SD_4_bits_Wide_bus
PC12.Signal=SDIO_CK
PC13.GPIOParameters=GPIO_Label
PC13.GPIO_Label=SAFE_S3C
PC13.Signal=GPIO_Input
PC14-OSC32_IN.GPIOParameters=GPIO_Label
PC14-OSC32_IN.GPIO_Label=SAFE_S4
PC14-OSC32_IN.Signal=GPIO_Input
PC15-OSC32_OUT.GPIOParameters=GPIO_PuPd,GPIO_Label
PC15-OSC32_OUT.GPIO_Label=BYP_BOT_FB
PC15-OSC32_OUT.GPIO_PuPd=GPIO_PULLDOWN
PC15-OSC32_OUT.Signal=GPIO_Input
PC2.GPIOParameters=GPIO_Label
PC2.GPIO_Label=SPI_MISO
PC2.Mode=Full_Duplex_Master
PC2.Signal=SPI2_MISO
PC3.GPIOParameters=GPIO_Label
PC3.GPIO_Label=SAFE_S3A
PC3.Signal=GPIO_Input
PC4.GPIOParameters=GPIO_Label
PC4.GPIO_Label=BYP_BOT_EN
PC4.Signal=GPIO_Output
PC5.GPIOParameters=GPIO_Label
PC5.GPIO_Label=BYP_TOP_EN
PC5.Signal=GPIO_Output
PC6.GPIOParameters=GPIO_Label
PC6.GPIO_Label=MODBUS_TX
PC6.Mode=Asynchronous
PC6.Signal=USART6_TX
PC7.GPIOParameters=GPIO_Label
PC7.GPIO_Label=MODBUS_RX
PC7.Mode=Asynchronous
PC7.Signal=USART6_RX
PC8.GPIOParameters=GPIO_Label
PC8.GPIO_Label=SDIO_D0
PC8.Mode=SD_4_bits_Wide_bus
PC8.Signal=SDIO_D0
PC9.GPIOParameters=GPIO_Label
PC9.GPIO_Label=SDIO_D1
PC9.Mode=SD_4_bits_Wide_bus
PC9.Signal=SDIO_D1
PD0.GPIOParameters=GPIO_Label
PD0.GPIO_Label=MODBUS_DE
PD0.Signal=GPIO_Output
PD1.GPIOParameters=GPIO_Label
PD1.GPIO_Label=SDIO_CD
PD1.Signal=GPIO_Input
PD10.GPIOParameters=GPIO_Label
PD10.GPIO_Label=OTR_EN
PD10.Signal=GPIO_Output
PD11.GPIOParameters=GPIO_Label
PD11.GPIO_Label=SPIF_SIO0
PD11.Mode=Single Bank 1
PD11.Signal=QUADSPI_BK1_IO0
PD12.GPIOParameters=GPIO_Label
PD12.GPIO_Label=SPIF_SIO1
PD12.Mode=Single Bank 1
PD12.Signal=QUADSPI_BK1_IO1
PD13.GPIOParameters=GPIO_Label
PD13.GPIO_Label=LPWM5_OUT
PD13.Signal=S_TIM4_CH2
PD14.GPIOParameters=GPIO_Label
PD14.GPIO_Label=LPWM6_OUT
PD14.Signal=S_TIM4_CH3
PD15.GPIOParameters=GPIO_Label
PD15.GPIO_Label=VLIGHT_EN
PD15.Signal=GPIO_Output
PD2.GPIOParameters=GPIO_Label
PD2.GPIO_Label=SDIO_CMD
PD2.Mode=SD_4_bits_Wide_bus
PD2.Signal=SDIO_CMD
PD3.GPIOParameters=GPIO_Label
PD3.GPIO_Label=SDIO_PWR
PD3.Signal=GPIO_Output
PD4.GPIOParameters=GPIO_Label
PD4.GPIO_Label=LIGHT1_EN
PD4.Signal=GPIO_Output
PD5.GPIOParameters=GPIO_Label
PD5.GPIO_Label=LIGHT2_EN
PD5.Signal=GPIO_Output
PD6.GPIOParameters=GPIO_Label
PD6.GPIO_Label=SAFE_S3B
PD6.Signal=GPIO_Input
PD7.GPIOParameters=GPIO_Label
PD7.GPIO_Label=SAFE_S3
PD7.Signal=GPIO_Input
PD8.GPIOParameters=GPIO_Label
PD8.GPIO_Label=BRK_FB1
PD8.Signal=GPIO_Input
PD9.GPIOParameters=GPIO_Label
PD9.GPIO_Label=OTR_FB
PD9.Signal=GPIO_Input
PE0.GPIOParameters=GPIO_Label
PE0.GPIO_Label=SPIF_NCS2
PE0.Signal=GPIO_Output
PE1.GPIOParameters=GPIO_Label
PE1.GPIO_Label=AUDIO_EN
PE1.Signal=GPIO_Output
PE10.GPIOParameters=GPIO_Label
PE10.GPIO_Label=VFD_I4
PE10.Signal=GPIO_Output
PE11.GPIOParameters=GPIO_Label
PE11.GPIO_Label=VFD_I5
PE11.Signal=GPIO_Output
PE12.GPIOParameters=GPIO_Label
PE12.GPIO_Label=VFD_I6
PE12.Signal=GPIO_Output
PE13.GPIOParameters=GPIO_Label
PE13.GPIO_Label=VFD_I7
PE13.Signal=GPIO_Output
PE14.GPIOParameters=GPIO_Label
PE14.GPIO_Label=VFD_STO
PE14.Signal=GPIO_Output
PE15.GPIOParameters=GPIO_Label
PE15.GPIO_Label=VFD_RUN
PE15.Signal=GPIO_Input
PE2.GPIOParameters=GPIO_Label
PE2.GPIO_Label=SPIF_SIO2
PE2.Mode=Single Bank 1
PE2.Signal=QUADSPI_BK1_IO2
PE3.GPIOParameters=GPIO_Label
PE3.GPIO_Label=LOAD_CLK
PE3.Signal=GPIO_Output
PE4.GPIOParameters=GPIO_Label
PE4.GPIO_Label=LOAD_DOUT
PE4.Signal=GPIO_Input
PE5.GPIOParameters=GPIO_Label
PE5.GPIO_Label=LOAD_NPDWN
PE5.Signal=GPIO_Input
PE6.GPIOParameters=GPIO_PuPd,GPIO_Label
PE6.GPIO_Label=BYP_TOP_FB
PE6.GPIO_PuPd=GPIO_PULLDOWN
PE6.Signal=GPIO_Input
PE7.GPIOParameters=GPIO_Label
PE7.GPIO_Label=VFD_I1
PE7.Signal=GPIO_Output
PE8.GPIOParameters=GPIO_Label
PE8.GPIO_Label=VFD_I2
PE8.Signal=GPIO_Output
PE9.GPIOParameters=GPIO_Label
PE9.GPIO_Label=VFD_I3
PE9.Signal=GPIO_Output
PH0-OSC_IN.GPIOParameters=GPIO_Label
PH0-OSC_IN.GPIO_Label=OSCI1
PH0-OSC_IN.Mode=HSE-External-Oscillator
PH0-OSC_IN.Signal=RCC_OSC_IN
PH1-OSC_OUT.GPIOParameters=GPIO_Label
PH1-OSC_OUT.GPIO_Label=OSCO1
PH1-OSC_OUT.Mode=HSE-External-Oscillator
PH1-OSC_OUT.Signal=RCC_OSC_OUT
RCC.HSE_VALUE=8000000
RCC.SYSCLKFreq_VALUE=160000000
RCC.SYSCLKSource=RCC_SYSCLKSOURCE_PLLCLK
board=custom

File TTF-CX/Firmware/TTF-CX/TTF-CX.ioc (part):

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Mcu.Name=STM32F446R(C-E)Tx
Mcu.Package=LQFP64
Mcu.UserName=STM32F446RCTx
PA0-WKUP.GPIOParameters=GPIO_Label
PA0-WKUP.GPIO_Label=SPIF_NCS2
PA0-WKUP.Signal=GPIO_Output
PA1.GPIOParameters=GPIO_Label
PA1.GPIO_Label=LOAD_DOUT
PA1.Signal=GPIO_Input
PA10.GPIOParameters=GPIO_Label
PA10.GPIO_Label=UART_RX
PA10.Mode=Asynchronous
PA10.Signal=USART1_RX
PA11.GPIOParameters=GPIO_Label
PA11.GPIO_Label=CAN_RX
PA11.Mode=CAN_Activate
PA11.Signal=CAN1_RX
PA12.GPIOParameters=GPIO_Label
PA12.GPIO_Label=CAN_TX
PA12.Mode=CAN_Activate
PA12.Signal=CAN1_TX
PA13.Mode=Serial_Wire
PA13.Signal=SYS_JTMS-SWDIO
PA14.Mode=Serial_Wire
PA14.Signal=SYS_JTCK-SWCLK
PA15.GPIOParameters=GPIO_Label
PA15.GPIO_Label=SPI_NSS
PA15.Mode=NSS_Signal_Hard_Output
PA15.Signal=SPI1_NSS
PA2.GPIOParameters=GPIO_Label
PA2.GPIO_Label=BYP_TOP_FB
PA2.Signal=GPIO_Input
PA3.GPIOParameters=GPIO_Label
PA3.GPIO_Label=NEOPIX_TX
PA3.Signal=S_TIM5_CH4
PA4.GPIOParameters=GPIO_Label
PA4.GPIO_Label=LOAD_CLK
PA4.Signal=GPIO_Output
PA5.GPIOParameters=GPIO_Label
PA5.GPIO_Label=VLIGHT_TRIM
PA5.Signal=COMP_DAC2_group
PA6.GPIOParameters=GPIO_Label
PA6.GPIO_Label=LPWM1_OUT
PA6.Signal=S_TIM3_CH1
PA7.GPIOParameters=GPIO_Label
PA7.GPIO_Label=LPWM2_OUT
PA7.Signal=S_TIM3_CH2
PA9.GPIOParameters=GPIO_Label
PA9.GPIO_Label=UART-TX
PA9.Mode=Asynchronous
PA9.Signal=USART1_TX
PB0.GPIOParameters=GPIO_Label
PB0.GPIO_Label=LPWM3_OUT
PB0.Signal=S_TIM3_CH3
PB1.GPIOParameters=GPIO_Label
PB1.GPIO_Label=LPWM4_OUT
PB1.Signal=S_TIM3_CH4
PB10.GPIOParameters=GPIO_Label
PB10.GPIO_Label=SCL
PB10.Mode=I2C
PB10.Signal=I2C2_SCL
PB12.GPIOParameters=GPIO_Label
PB12.GPIO_Label=BOT_UZONE
PB12.Signal=GPIO_Input
PB13.GPIOParameters=GPIO_Label
PB13.GPIO_Label=BYP_TOP_EN
PB13.Signal=GPIO_Output
PB14.GPIOParameters=GPIO_Label
PB14.GPIO_Label=S3C
PB14.Signal=GPIO_Input
PB2.GPIOParameters=GPIO_Label
PB2.GPIO_Label=SPIF_SCLK
PB2.Mode=Single Bank 1 2IOs
PB2.Signal=QUADSPI_CLK
PB3.GPIOParameters=GPIO_Label
PB3.GPIO_Label=SPI_SCK
PB3.Mode=Full_Duplex_Master
PB3.Signal=SPI1_SCK
PB4.GPIOParameters=GPIO_Label
PB4.GPIO_Label=SPI_MISO
PB4.Mode=Full_Duplex_Master
PB4.Signal=SPI1_MISO
PB5.GPIOParameters=GPIO_Label
PB5.GPIO_Label=SPI_MOSI
PB5.Mode=Full_Duplex_Master
PB5.Signal=SPI1_MOSI
PB6.GPIOParameters=GPIO_Label
PB6.GPIO_Label=SPIF_NCS
PB6.Mode=Single Bank 1 2IOs
PB6.Signal=QUADSPI_BK1_NCS
PB7.GPIOParameters=GPIO_Label
PB7.GPIO_Label=LPWM5_OUT
PB7.Signal=S_TIM4_CH2
PB8.GPIOParameters=GPIO_Label
PB8.GPIO_Label=EL_PWM_OUT
PB8.Signal=S_TIM4_CH3
PC0.GPIOParameters=GPIO_Label
PC0.GPIO_Label=S4
PC0.Signal=GPIO_Input
PC1.GPIOParameters=GPIO_Label
PC1.GPIO_Label=BYP_BOT_FB
PC1.Signal=GPIO_Input
PC10.GPIOParameters=GPIO_Label
PC10.GPIO_Label=SPIF_SIO1
PC10.Mode=Single Bank 1 2IOs
PC10.Signal=QUADSPI_BK1_IO1
PC12.GPIOParameters=GPIO_Label
PC12.GPIO_Label=SDA
PC12.Mode=I2C
PC12.Signal=I2C2_SDA
PC13.GPIOParameters=GPIO_Label
PC13.GPIO_Label=DEBUG
PC13.Signal=GPIO_Output
PC14-OSC32_IN.GPIOParameters=GPIO_Label
PC14-OSC32_IN.GPIO_Label=S3A
PC14-OSC32_IN.Signal=GPIO_Input
PC15-OSC32_OUT.GPIOParameters=GPIO_Label
PC15-OSC32_OUT.GPIO_Label=BYP_BOT_EN
PC15-OSC32_OUT.Signal=GPIO_Output
PC2.GPIOParameters=GPIO_Label
PC2.GPIO_Label=S3
PC2.Signal=GPIO_Input
PC3.GPIOParameters=GPIO_Label
PC3.GPIO_Label=VLIGHT_EN
PC3.Signal=GPIO_Output
PC4.GPIOParameters=GPIO_Label
PC4.GPIO_Label=LOAD_NPWDN
PC4.Signal=GPIO_Output
PC5.GPIOParameters=GPIO_Label
PC5.GPIO_Label=TOP_UZONE
PC5.Signal=GPIO_Input
PC9.GPIOParameters=GPIO_Label
PC9.GPIO_Label=SPIF_SIO0
PC9.Mode=Single Bank 1 2IOs
PC9.Signal=QUADSPI_BK1_IO0
PH0-OSC_IN.Signal=RCC_OSC_IN
PH1-OSC_OUT.Signal=RCC_OSC_OUT
board=custom
